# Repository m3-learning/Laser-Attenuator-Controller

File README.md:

# Laser-Attenuator-Controller

Open source laser attenuator controller

Created by: The M3 Learning Group

All designs and code by: Ryan Forelli

## Components needed for PCB assembly
-   1x Custom PCB
-   1x A4988 stepper motor drivers
-   1x ATmega328P AVR microcontroller
-   1x Male & female pin header set
-   1x through hole pushbutton
-   1x 16 MHz crystal oscillator
-   2x 22pF ceramic capacitors
-   1x 10uF electrolytic capacitor
-   1x 100uF electrolytic capacitor
-   2x 100nF capacitors
-   3x 10k through-hole resistor
-   1x Assorted solid-core jumper wires
-   1x [Standoffs][0] (optional)
-   1x Custom back plate (optional)
-   1x [USB to TTL Adapter][2]
-   1x PN2222 transistor
-   1x 1N400X series diode
-   1x 5V SRD-05VDC-SL-C relay
-   1x CH330N USB to serial chip (optional if using USB to TTL Adapter)
-   1x 5.5x2.1 DC power port
-   1x USB type B female port

Our open source PCB and firmware can be used to control an attenuator controller to adjust the power output of a laser for applications such as pulsed laser deposition. The program attenuator_control.exe can be used to communicate with the ATmega328p microcontroller to control the attenuator. The LabVIEW and C++ source code is available in the repository.

## Installation Notes
-   Supply PCB with 5V from USB to TTL Adapter.
-   Supply stepper motor controller and relay with 24V.

<!-- ## Usage Instructions
-   Power PLD Controller module
-   Open LabVIEW pldsyscontrol.exe and run Virtual Instrument (VI)
-   Select COM port
-   Home raster motor (does not home to a specific target)
-   Select target and begin use -->

[0]: https://www.amazon.com/Csdtylh-Male-Female-Standoff-Stainless-Assortment/dp/B06Y5TJXY1/ref=sr_1_3?dchild=1&keywords=standoff&qid=1620104015&sr=8-3
[1]: https://www.amazon.com/gp/product/B074M15FS1/ref=ppx_yo_dt_b_asin_title_o02_s00?ie=UTF8&psc=1
[2]: https://www.amazon.com/DSD-TECH-SH-U09C2-Debugging-Programming/dp/B07TXVRQ7V/ref=sr_1_8?dchild=1&keywords=FT232RL+USB+to+Serial&qid=1616559163&s=electronics&sr=1-8#customerReviews

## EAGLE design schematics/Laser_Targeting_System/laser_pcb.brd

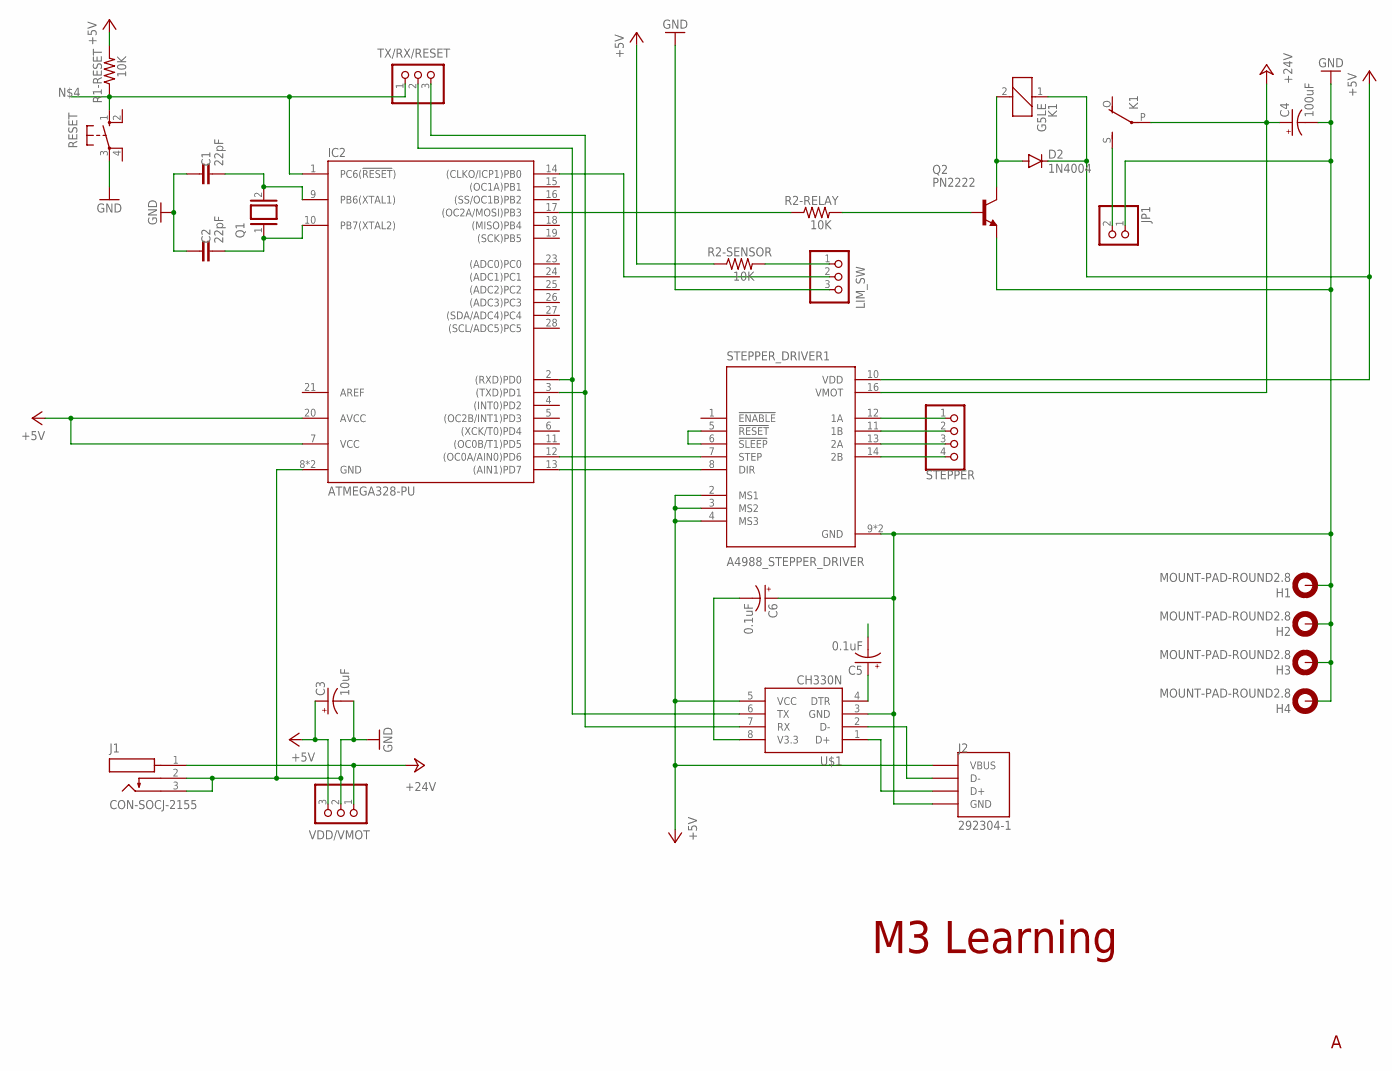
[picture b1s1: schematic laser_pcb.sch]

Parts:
C1, C2: 22pF; CAP-PTH-2.54
C3: 10uF; CPOL-RADIAL-2.5MM-5MM
C4: 100uF; CPOL-RADIAL-2.5MM-5MM
C5, C6: 0.1uF; CPOL-RADIAL-2.5MM-5MM
D2: 1N4004; DO41-10
H1, H2, H3, H4: MOUNT-PAD-ROUND2.8; 2,8-PAD
IC2: ATMEGA328-PU; DIL28
J1: CON-SOCJ-2155; GRAVITECH_CON-SOCJ-2155
J2: 292304-1; TE_292304-1
JP1: PINHD-1X2; 1X02
K1: G5LE
LIM_SW: PINHD-1X3; 1X03
Q1: XTAL/S; QS
Q2: PN2222; TO92
R1-RESET, R2-RELAY, R2-SENSOR: 10K; 0204/7
RESET: 10-XX; B3F-10XX
STEPPER: PINHD-1X4; 1X04
STEPPER_DRIVER1: A4988_STEPPER_DRIVER; MODULE_A4988_STEPPER_MOTOR_DRIVER_CARRIER
TX/RX/RESET: PINHD-1X3; 1X03
U$1: CH330N; SOIC8
VDD/VMOT: PINHD-1X3; 1X03

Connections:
+5V: C3.1 (+), D2.C, IC2.7 (VCC), IC2.20 (AVCC), J2.1 (VBUS), K1.1, R1-RESET.2, R2-SENSOR.1, STEPPER_DRIVER1.2 (MS1), STEPPER_DRIVER1.3 (MS2), STEPPER_DRIVER1.4 (MS3), STEPPER_DRIVER1.10 (VDD), U$1.5 (VCC), VDD/VMOT.3
+24V: C4.1 (+), J1.1, K1.P, STEPPER_DRIVER1.16 (VMOT), VDD/VMOT.1
GND: C1.1, C2.1, C3.2 (-), C4.2 (-), C6.1 (+), H1.B2,8, H2.B2,8, H3.B2,8, H4.B2,8, IC2.8 (GND), IC2.22 (GND), J1.2, J1.3, J2.4 (GND), JP1.1, LIM_SW.3, Q2.1 (E), RESET.3, STEPPER_DRIVER1.9 (GND), STEPPER_DRIVER1.15 (GND), U$1.3 (GND), VDD/VMOT.2
unnamed: C1.2, IC2.9 (PB6(XTAL1)), Q1.2
unnamed: C2.2, IC2.10 (PB7(XTAL2)), Q1.1
unnamed: C5.2 (-), IC2.1 (PC6(!RESET!)), R1-RESET.1, RESET.1 (S), TX/RX/RESET.1
unnamed: STEPPER_DRIVER1.5 (!RESET), STEPPER_DRIVER1.6 (!SLEEP)
unnamed: IC2.13 ((AIN1)PD7), STEPPER_DRIVER1.8 (DIR)
unnamed: IC2.12 ((OC0A/AIN0)PD6), STEPPER_DRIVER1.7 (STEP)
unnamed: STEPPER.1, STEPPER_DRIVER1.12 (1A)
unnamed: STEPPER.2, STEPPER_DRIVER1.11 (1B)
unnamed: STEPPER.3, STEPPER_DRIVER1.13 (2A)
unnamed: STEPPER.4, STEPPER_DRIVER1.14 (2B)
unnamed: LIM_SW.1, R2-SENSOR.2
unnamed: Q2.2 (B), R2-RELAY.2
unnamed: IC2.14 ((CLKO/ICP1)PB0), LIM_SW.2
unnamed: JP1.2, K1.S
unnamed: D2.A, K1.2, Q2.3 (C)
unnamed: IC2.17 ((OC2A/MOSI)PB3), R2-RELAY.1
unnamed: J2.2 (D-), U$1.2 (D-)
unnamed: J2.3 (D+), U$1.1 (D+)
unnamed: C5.1 (+), U$1.4 (DTR)
unnamed: C6.2 (-), U$1.8 (V3.3)
unnamed: IC2.2 ((RXD)PD0), TX/RX/RESET.2, U$1.6 (TX)
unnamed: IC2.3 ((TXD)PD1), TX/RX/RESET.3, U$1.7 (RX)

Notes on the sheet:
M3 Learning

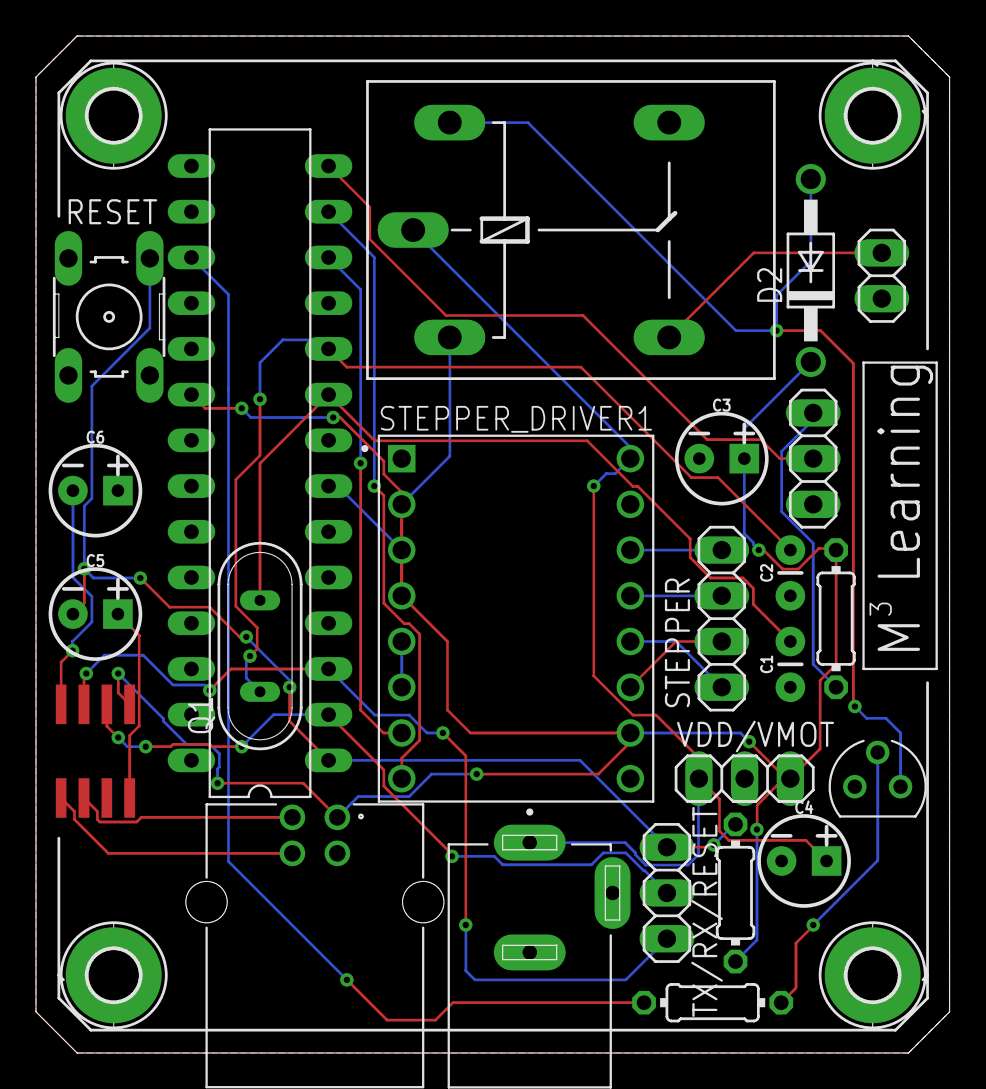
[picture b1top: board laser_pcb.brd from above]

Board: 2 copper layers, 50.8 x 56.5 mm, 28 parts (0 on the bottom side), 25 nets.

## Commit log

2021-06-21 license
2021-06-23 labview interface
2021-06-23 lv interface
2021-06-23 source code
2021-06-23 fixed labview code
2021-06-26 updated schematic
2021-06-26 minor edit
2021-07-06 model

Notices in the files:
schematics/Laser_Targeting_System/laser_pcb.brd:
Released under BSD-3 License.
parts and their libraries:
SparkFun-Capacitors: Licensing: Creative Commons ShareAlike 4.0 International - https://creativecommons.org/licenses/by-sa/4.0
